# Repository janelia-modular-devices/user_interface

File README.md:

# user_interface

Authors:

    Peter Polidoro <polidorop@janelia.hhmi.org>

License:

    BSD

## More Detailed Help on Installation and Usage

[modular-devices](https://github.com/janelia-modular-devices/modular-devices)

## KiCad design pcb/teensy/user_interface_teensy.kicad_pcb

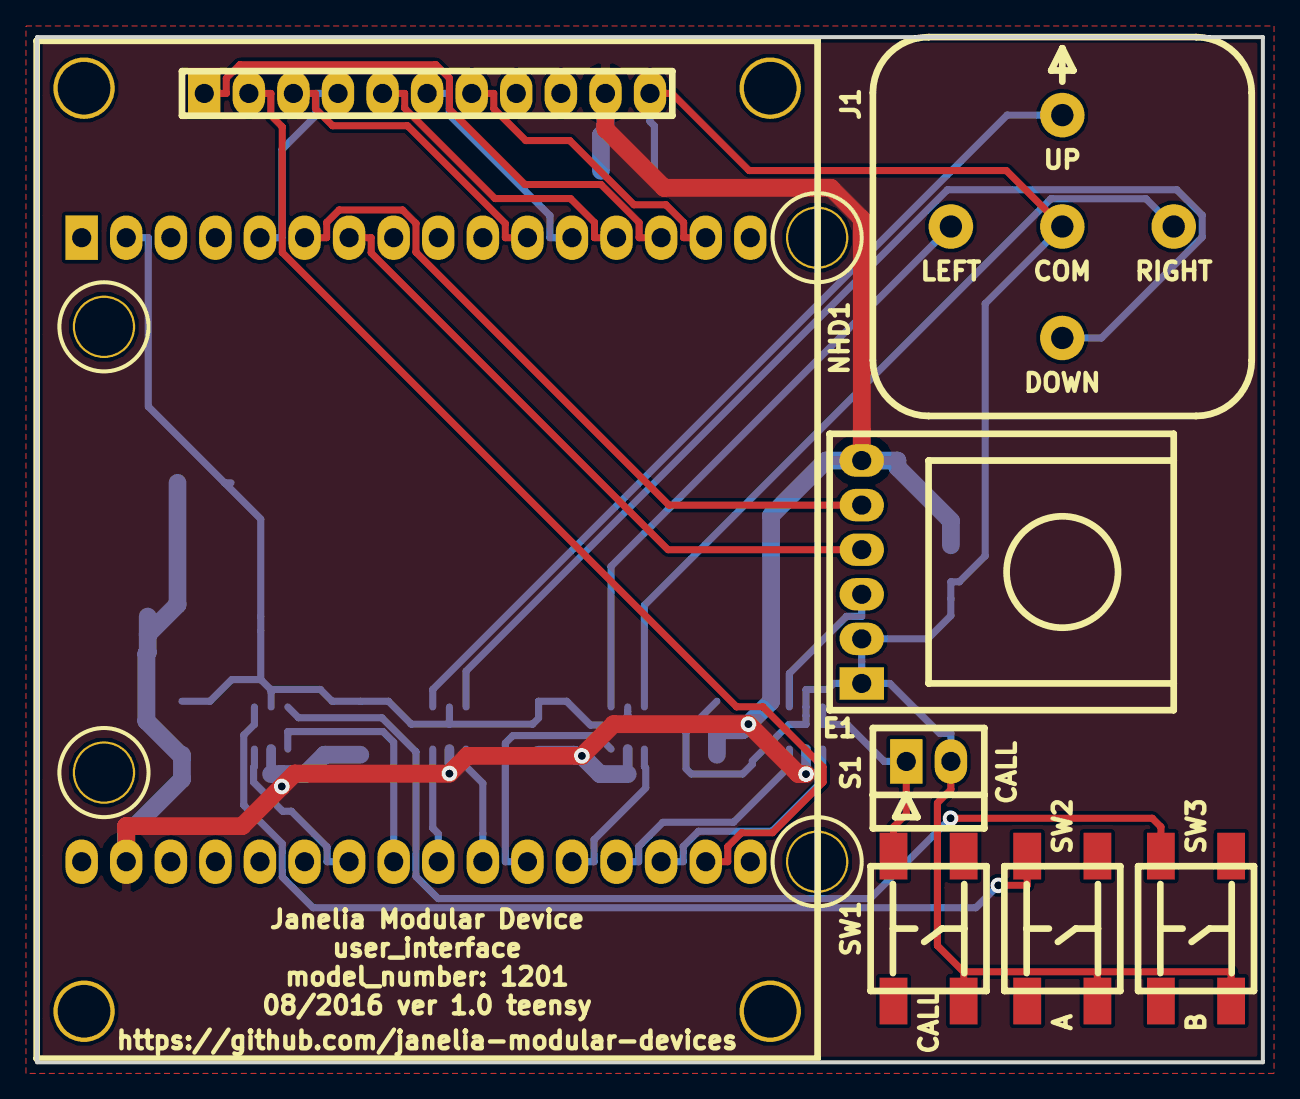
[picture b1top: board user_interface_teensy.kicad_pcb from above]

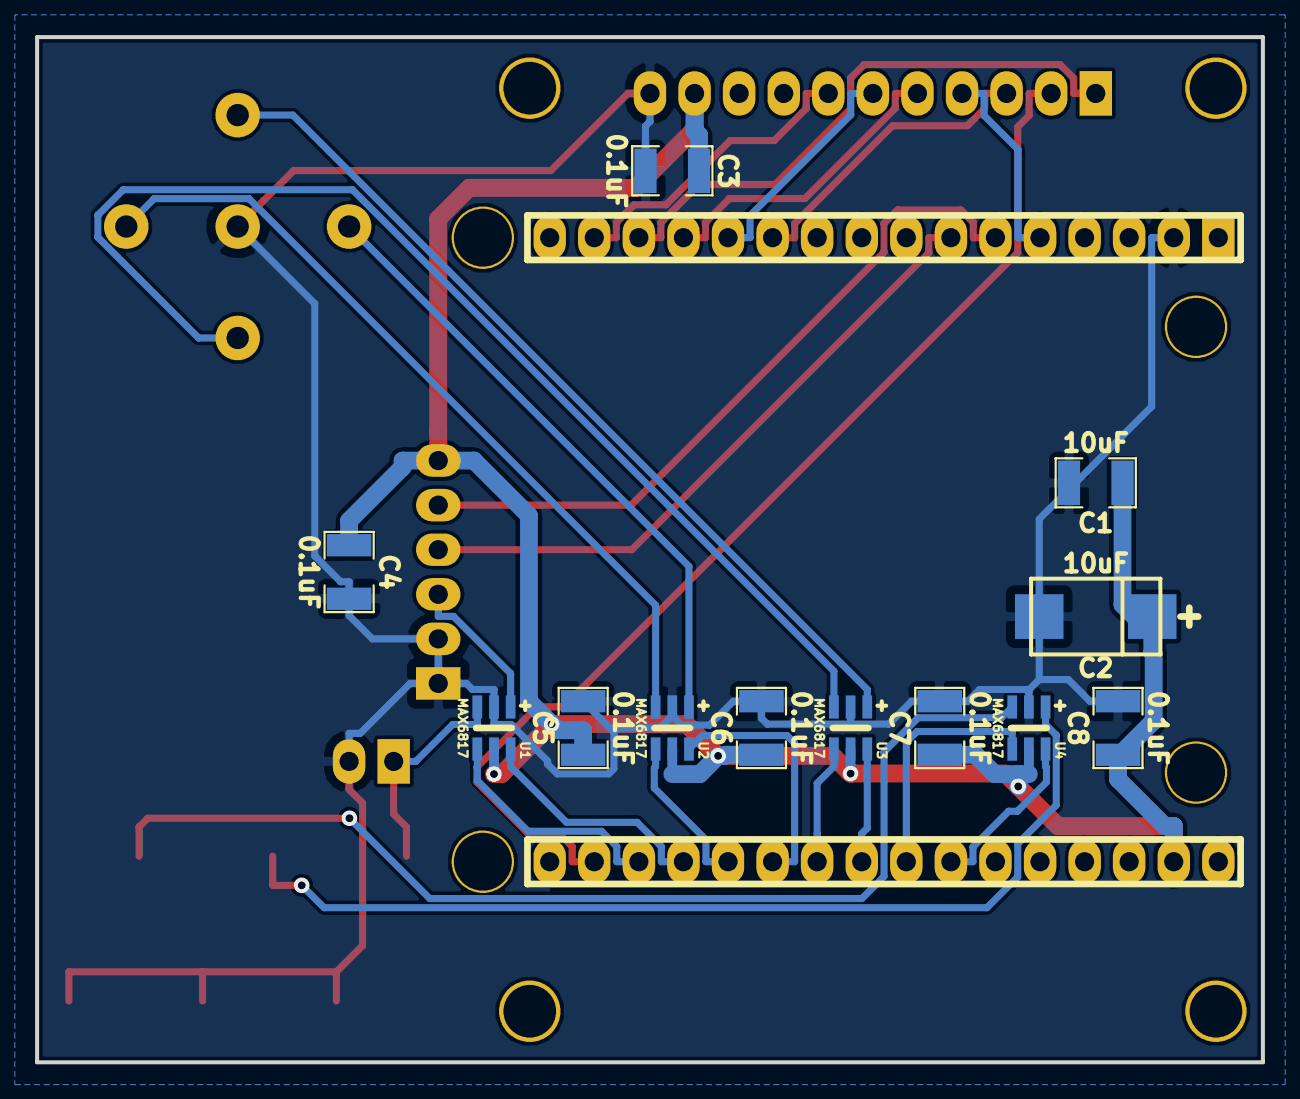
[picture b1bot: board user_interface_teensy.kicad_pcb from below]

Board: 2 copper layers, 69.8 x 58.4 mm, 20 parts (12 on the bottom side), 27 nets.

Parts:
C1: 10uF; SM1210
C2: 10uF; SM2917_POL
C3, C4, C5, C6, C7, C8: 0.1uF; SM1210
E1: ENCODER_62A11-02-P; ENCODER_62AVD
J1: JOYSTICK
MDT1: MODULAR_DEVICE_TEENSY_MALE
NHD1: NHD-ASC3-169; NHD-ASC3
S1: HEADER_01X02_SHR; Header_Shrouded_2_Pin
SW1, SW2, SW3: KT_SWITCH
U1, U2, U3, U4: MAX6817

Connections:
/BTN_A: MDT1.21, U4.6
/BTN_B: MDT1.20, U4.4
/BTN_CALL: MDT1.14, U1.4
/BTN_ENC: MDT1.15, U1.6
/B_BTN_A: SW2.2, U4.1
/B_BTN_B: SW3.2, U4.3
/B_BTN_CALL: S1.1, SW1.2, U1.3
/B_BTN_ENC: E1.3, U1.1
/B_DOWN: J1.D, U3.3
/B_LEFT: J1.L, U2.1
/B_RIGHT: J1.R, U2.3
/B_UP: J1.U, U3.1
/DOWN: MDT1.18, U3.4
/ENC_A: E1.5, MDT1.3
/ENC_B: E1.4, MDT1.4
/LEFT: MDT1.17, U2.6
/MISO: MDT1.12, NHD1.7
/MOSI: MDT1.11, NHD1.1
/OLEDCS: MDT1.10, NHD1.5
/OLEDDC: MDT1.29, NHD1.3
/RESET: MDT1.2, NHD1.4
/RIGHT: MDT1.16, U2.4
/SCK: MDT1.13, NHD1.2
/SDCS: MDT1.9, NHD1.6
/UP: MDT1.19, U3.6
GND: C1.2, C2.2, C3.2, C4.2, C5.2, C6.2, C7.2, C8.2, E1.1, E1.2, J1.COM, MDT1.GND, NHD1.11, S1.2, SW1.3, SW2.3, SW3.3, U1.2, U2.2, U3.2, U4.2
VEE: C1.1, C2.1, C3.1, C4.1, C5.1, C6.1, C7.1, C8.1, E1.6, MDT1.VEE, NHD1.10, U1.5, U2.5, U3.5, U4.5

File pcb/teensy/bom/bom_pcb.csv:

Item,Reference(s),Value,Quantity,Description,PartNumber,Vendor
1,C1,10uF,1,CAP CER 10UF 50V 10% X7S 1210,445-4536-1-ND,digikey
2,C2,10uF_2917_POL,1,CAP TANT 10UF 35V 10% 2917,399-8527-1-ND,digikey
3,C3 C4 C5 C6 C7 C8,0.1uF,6,CAP CER 0.1UF 50V 10% X7R 1210,478-3586-1-ND,digikey
4,E1,ENCODER_62A11-02-P,1,ENCODER OPT 1/2in 32POS PB PC MNT,GH7384-ND,digikey
5,J1,JOYSTICK,1,Navigation Switch 2 Axis Digital,GH7455-ND,digikey
6,MDT1,MODULAR_DEVICE_TEENSY_MALE,2,16 Position Header Through Hole Male Pins,S1011E-16-ND,digikey
7,NHD1,NHD-ASC3-169,1,1.69in SERIAL COLOR OLED,NHD-1.69-160128ASC3-ND,digikey
8,S1,HEADER_01X02_SHR,1,CONN HEADER 2POS .100 VERT GOLD,WM4800-ND,digikey
9,SW1 SW2 SW3,KT_SWITCH,3,SWITCH TACTILE SPST-NO 1VA 32V,CKN1860CT-ND,digikey
10,U1 U2 U3 U4,MAX6817,4,IC DEBOUNCER SWITCH DUAL SOT23-6,MAX6817EUT+TCT-ND,digikey

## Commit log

2016-07-26 Initial commit.
2016-07-26 Progress towards schematic v1.0.
2016-07-27 Added encoder.
2016-08-25 Progress towards teensy v1.0.
2016-08-26 Finished pcb v1.0.
2016-09-19 Updated spaces around pointers and references.
2016-09-21 pcb -> hardware.
2017-03-29 Updated documentation.
2018-04-12 *.md -> *.org.
2018-08-12 polidorop@janelia.hhmi.org -> peterpolidoro@gmail.com
2018-08-27 Combined software and hardware licenses.
2021-09-17 Update email address
